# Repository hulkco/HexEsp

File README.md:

# HexEsp is a Breakout Board of amazing ESP8266 in a nice Hexagon PCB.

First thank you for visiting my project, I tell them that I'm not an electronics engineer, I'm just an amateur (passionate) the maker movement, and this is the second board that I make, I am supporting the designs of @Adafruit and @NodeMCU.

Following the philosophy of Open Software and Hardaware and the teachings of Master @Obijuan_cube, published under the Free license.

ch340 directory include a  ch340g Serial-Uart version of HexEsp
cp2104 directory include a  cp2104 Serial-Uart version of HexEsp

License
=======

GPL license or Creative Commons Attribution-shareAlike  (Copyleft)

Authors
=======
* Gustavo Salvador Reynaga Aguilar

Credits
=======
Espressif
Adafruit
NodeMCU

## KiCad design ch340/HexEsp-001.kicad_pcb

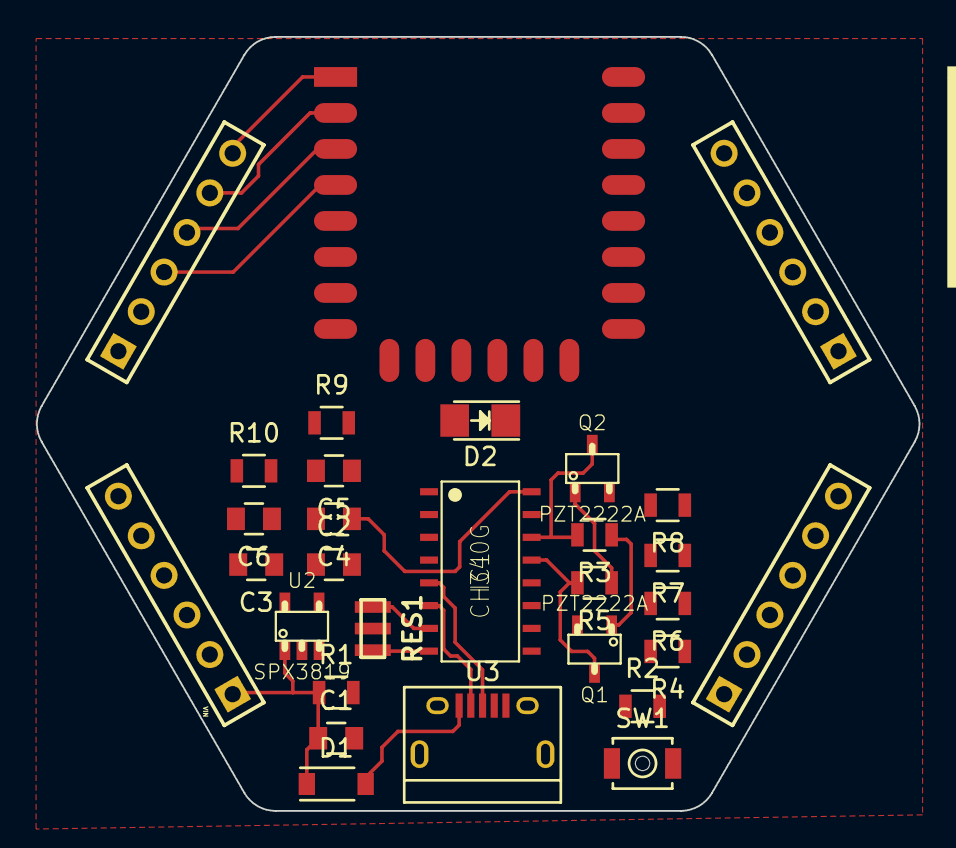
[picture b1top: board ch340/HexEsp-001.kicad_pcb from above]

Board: 2 copper layers, 49.0 x 43.0 mm, 30 parts (0 on the bottom side), 30 nets.

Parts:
C1, C2, C4: 10uF; C_0805
C3: 1uF; C_0805
C5, C6: 100nF; C_0805
D1: MBR120; SOD-123
D2: PURPLE; LED_1206
IC1: CH340G; SOP-16
J1, J2, J3, J4: 1x6_female_pin_Header_2.54mm; 1x6-Socket-header-2.54mm
Q1, Q2: PZT2222A; AB2_SOT23-3
R1, R2, R3, R5: 10K; R_0805
R4, R6, R7, R8: 1K; R_0805
R9, R10: 470; R_0805
RES1: AB2_RES_3P; murata-resonator_SMD_CSTCE8M00G55-R0
SW1: RESET; SW_SPST_B3U-1000P-B
U1: ESP-12E
U2: SPX3819; AB2_SOT23-5
U3: MICRO-B_USB; USB_Micro-B

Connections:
+3V3: C2.1, C3.1, D2.2, J2.2, J4.4, R2.1, R4.2, R6.2, U1.8, U2.5
/ADC: J1.5, U1.2
/CH_PD: J1.4, R6.1, U1.3
/D+: IC1.5, U3.3
/D-: IC1.6, U3.2
/DTR: IC1.13, Q1.3, R5.2
/EN: R1.2, U2.3
/GPIO0: J3.2, Q1.2, R8.1, U1.18
/GPIO2: J3.1, R4.1, U1.17
/GPIO4: J3.3, U1.19
/GPIO5: J3.4, U1.20
/GPIO12: J1.2, J2.5, U1.6
/GPIO13: J2.4, U1.7
/GPIO14: J2.6, U1.5
/GPIO15: J4.6, R7.2, U1.16
/GPIO16: J1.3, U1.4
/RESET: J1.6, Q2.2, R2.2, SW1.2, U1.1
/RTS: IC1.14, Q2.3, R3.2
/RXD: J3.5, R9.1, U1.21
/TXD: J3.6, R10.1, U1.22
/XI: IC1.7, RES1.1
/XO: IC1.8, RES1.3
GND: C1.2, C2.2, C3.2, C4.2, C5.2, C6.2, IC1.1, J1.1, J2.3, J4.5, R7.1, RES1.2, SW1.1, U1.15, U2.2, U3.5
unnamed: C5.1, IC1.4
unnamed: D2.1, R8.2
unnamed: IC1.2, R9.2
unnamed: IC1.3, R10.2
unnamed: Q1.1, R3.1
unnamed: Q2.1, R5.1
VBUS: C1.1, C4.1, C6.1, D1.1, D1.2, IC1.16, J2.1, J4.1, R1.1, U2.1, U3.1

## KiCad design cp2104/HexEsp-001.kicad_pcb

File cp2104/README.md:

# HexEsp is a Breakout Board of amazing ESP8266 in a nice Hexagon PCB.

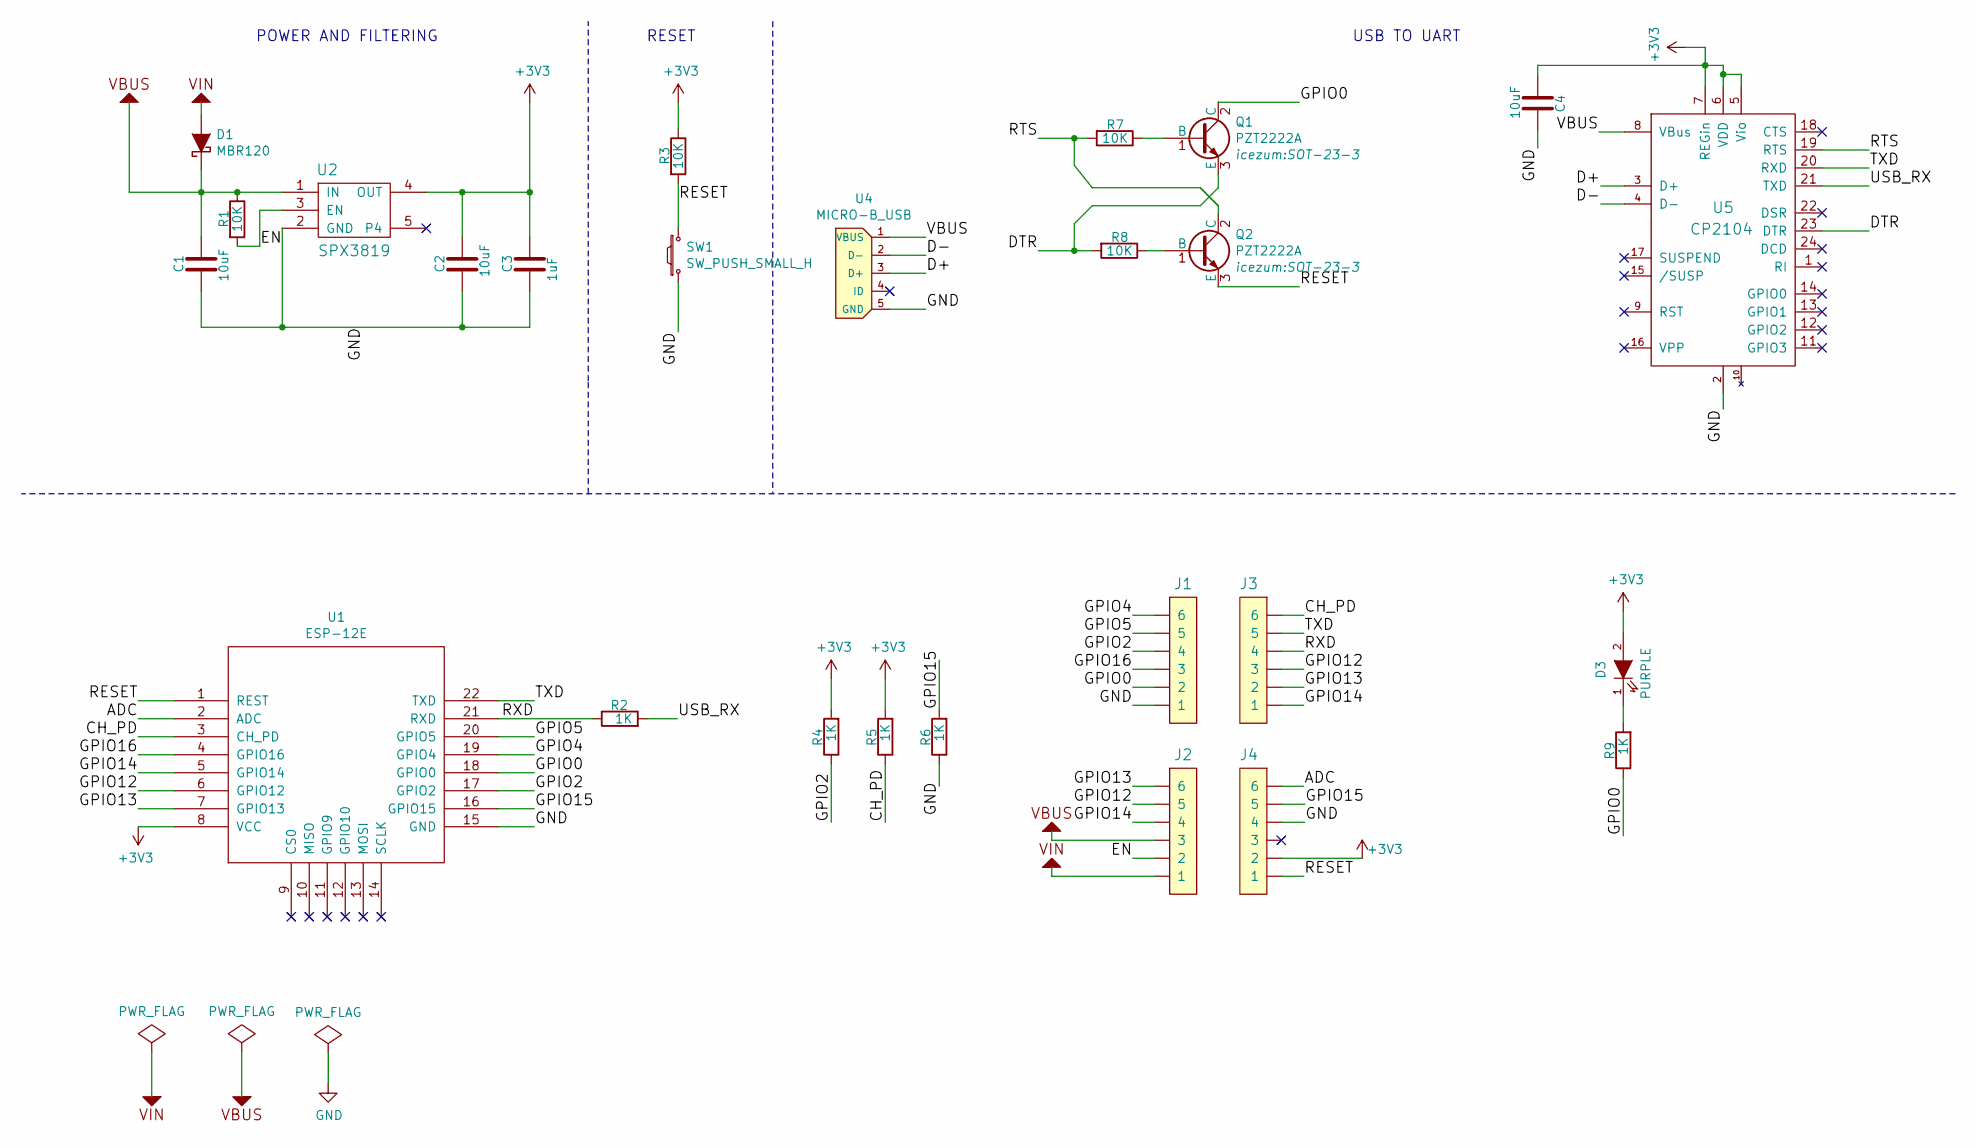
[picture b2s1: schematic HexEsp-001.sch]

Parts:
C1, C2, C4: 10uF; C_0805_HandSoldering
C3: 1uF; C_0805_HandSoldering
D1: MBR120; SOD-123
D3: PURPLE; LED_1206_Hand_Soldering
J1, J2, J3, J4: 1x6_female_pin_Header_2.54mm; 1x6-Socket-header-2.54mm
Q1, Q2: PZT2222A; SOT-23-3
R1, R3, R7, R8: 10K; R_0805_HandSoldering
R2, R4, R5, R6, R9: 1K; R_0805_HandSoldering
SW1: SW_PUSH_SMALL_H; SW_SPST_TL3342
U1: ESP-12E
U2: SPX3819; AB2_SOT23-5
U4: MICRO-B_USB; USB_Micro-B
U5: CP2104; QFN-24-1EP_4x4mm_Pitch0.5mm

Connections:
/ADC: J4.6, U1.2 (ADC)
/CH_PD: J3.6, R5.1, U1.3 (CH_PD)
/D+: U4.3 (D+), U5.3 (D+); also elsewhere on the board
/D-: U4.4 (ID); also elsewhere on the board
/DTR: Q1.3 (E), R8.2, U4.23, U5.23 (DTR)
/EN: J2.2, R1.2, U2.3 (EN)
/GPIO0: J1.2, Q1.2 (C), R9.1, U1.18 (GPIO0)
/GPIO2: J1.4, R4.1, U1.17 (GPIO2)
/GPIO4: J1.6, U1.19 (GPIO4)
/GPIO5: J1.5, U1.20 (GPIO5)
/GPIO12: J2.5, J3.3, U1.6 (GPIO12)
/GPIO13: J2.6, J3.2, U1.7 (GPIO13)
/GPIO14: J2.4, J3.1, U1.5 (GPIO14)
/GPIO15: J4.5, R6.2, U1.16 (GPIO15)
/GPIO16: J1.3, U1.4 (GPIO16)
/RESET: J4.1, Q2.3 (E), R3.2, SW1.2, U1.1 (REST)
/RTS: Q2.2 (C), R7.2, U4.19, U5.19 (RTS)
/RXD: J3.4, R2.1, U1.21 (RXD)
/TXD: J3.5, U1.22 (TXD), U4.20, U5.20 (RXD)
/USB_RX: R2.2, U4.21, U5.21 (TXD)
unnamed 20: D3.1 (K), R9.2; also elsewhere on the board
unnamed: Q1.1 (B), R7.1
unnamed: Q2.1 (B), R8.1
unnamed: U4.1 (VBUS), U5.8 (VBus)
VBUS: C1.1, D1.1 (K), J2.3, R1.1, U2.1 (IN), U4.8; also elsewhere on the board
VIN: D1.2 (A), J2.1

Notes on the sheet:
POWER AND FILTERING
USB TO UART
RESET

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
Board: 2 copper layers, 26 parts (0 on the bottom side), 27 nets, no tracks yet.

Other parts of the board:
D2: PURPLE; LED_1206
U3: MICRO-B_USB; USB_Micro-B

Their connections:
/D+: U3.3; also elsewhere on the board
/D-: U3.2; also elsewhere on the board
unnamed 20: D2.1; also elsewhere on the board
VBUS: U3.1; also elsewhere on the board

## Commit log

2016-10-04 HexEsp alfa release
2016-10-05 Re-organized directory
2016-10-09 Some litle changes
